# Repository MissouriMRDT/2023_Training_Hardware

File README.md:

# 2023_Training_Hardware
Useless Schematics and PCB Layouts for Training Purposes

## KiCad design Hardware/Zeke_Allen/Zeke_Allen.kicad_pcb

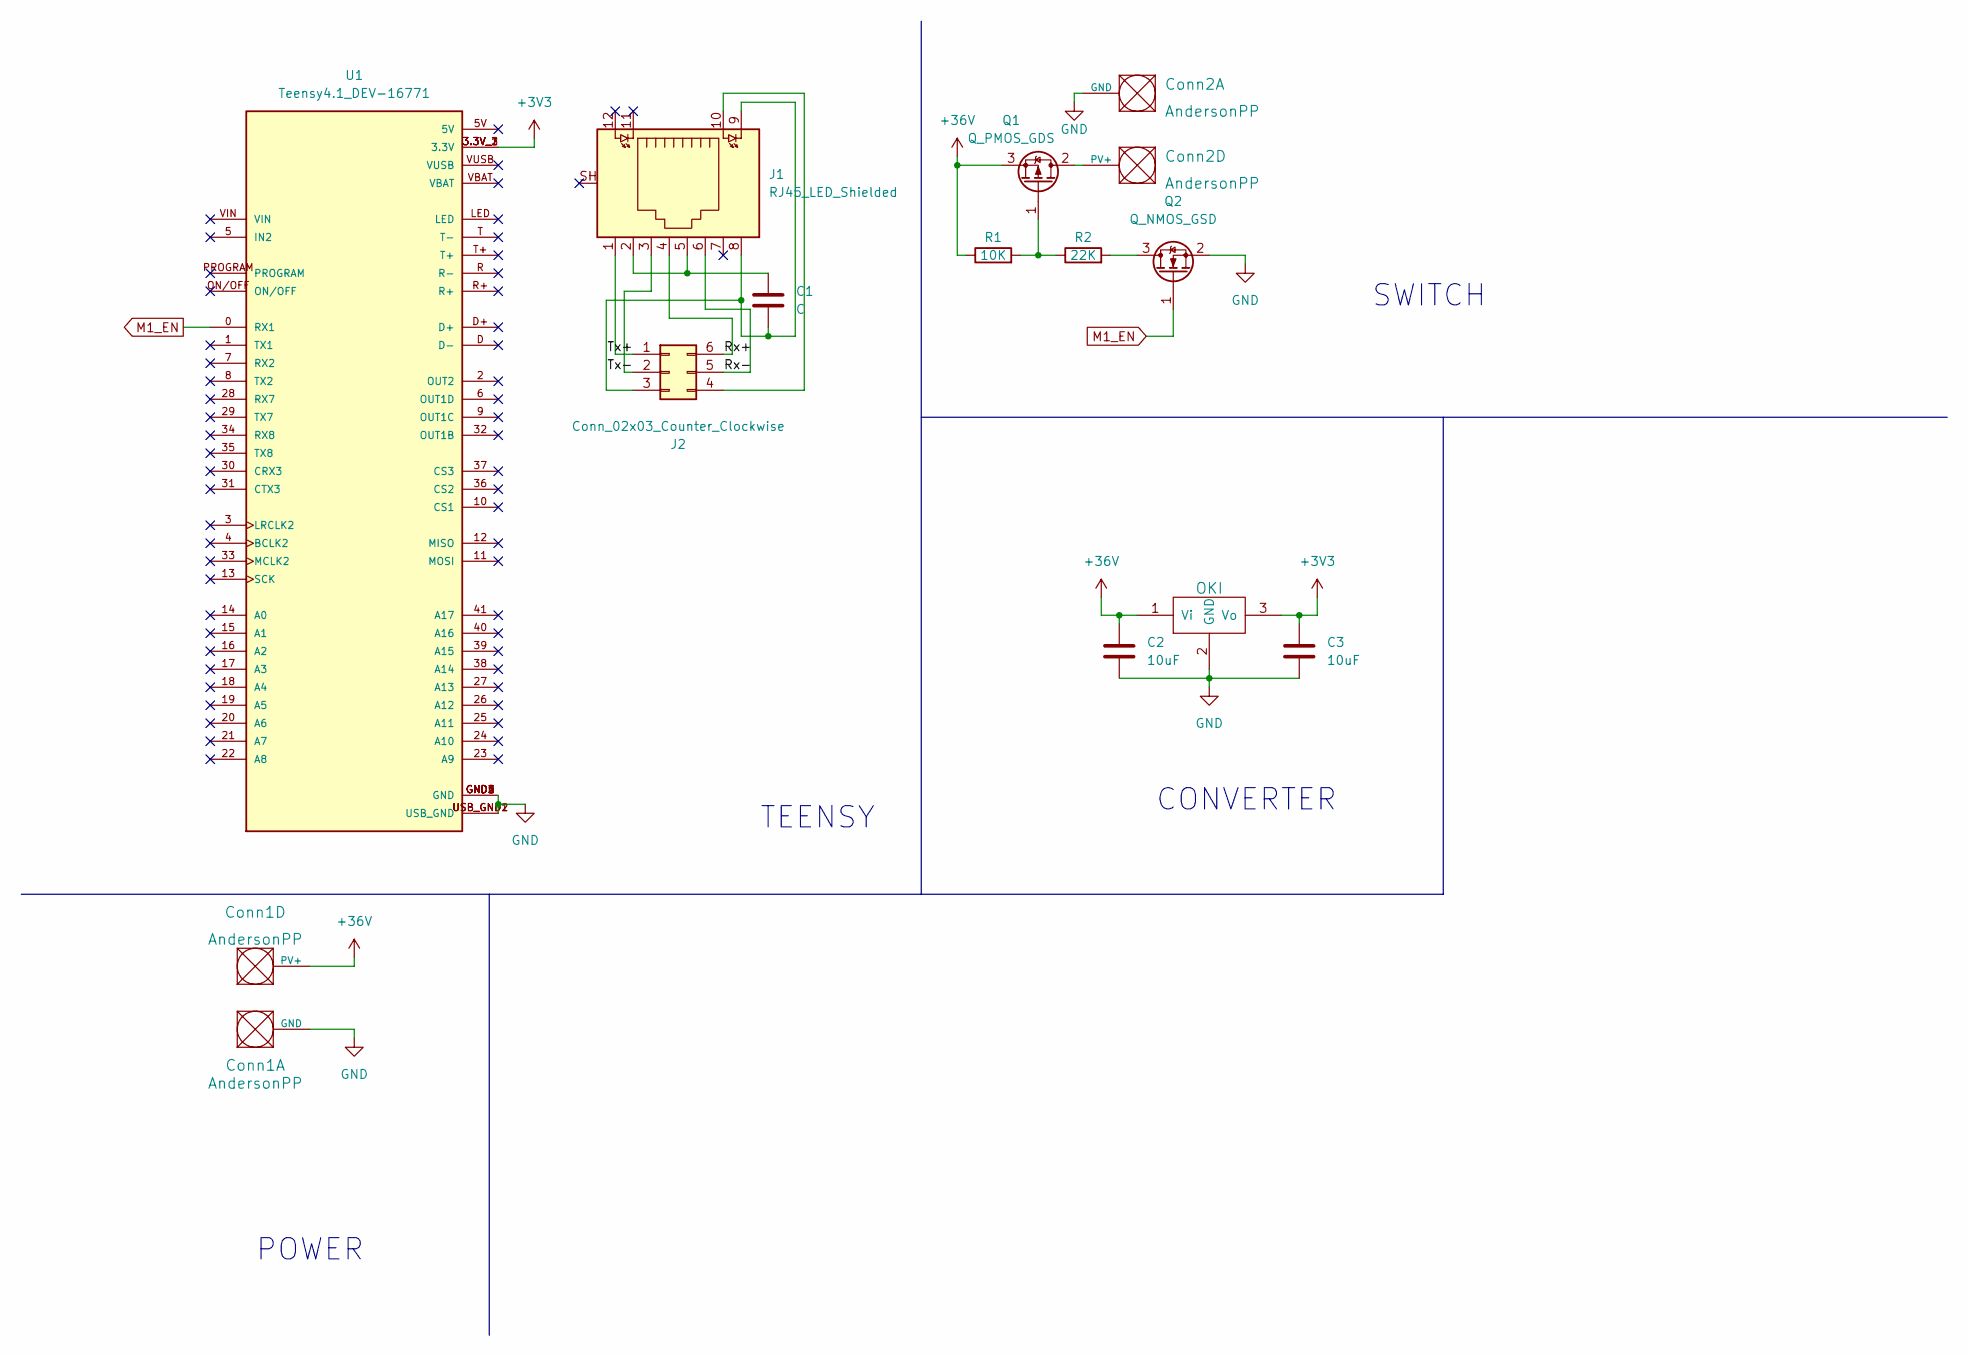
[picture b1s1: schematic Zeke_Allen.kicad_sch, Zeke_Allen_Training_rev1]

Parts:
C1: C; C_0603_1608Metric_Pad1.08x0.95mm_HandSolder
C2, C3: 10uF; C_0603_1608Metric_Pad1.08x0.95mm_HandSolder
Conn1, Conn2: AndersonPP; Square_Anderson_2_H_Side_By_Side_PV
J1: RJ45_LED_Shielded; RJ45_Teensy
J2: Conn_02x03_Counter_Clockwise; PinHeader_2x03_P2.00mm_Vertical
Q1: Q_PMOS_GDS; TO-252-2
Q2: Q_NMOS_GSD; SOT-23
R1: 10K; R_0603_1608Metric_Pad0.98x0.95mm_HandSolder
R2: 22K; R_0603_1608Metric_Pad0.98x0.95mm_HandSolder
U1: Teensy4.1_DEV-16771; Teensy_4_1_Vertical; PARTREV 4.1
U2: OKI; OKI_Horizontal

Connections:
+3V3: C3.1, U1.3.3V_1 (3.3V), U1.3.3V_2 (3.3V), U1.3.3V_3 (3.3V), U2.3 (Vo)
+36V: C2.1, Conn1.4 (PV+), Q1.3 (S), R1.1, U2.1 (Vi)
/Rx+: J1.4, J2.6
/Rx-: J1.6, J2.5
/Tx+: J1.1, J2.1
/Tx-: J1.3, J2.2
GND: C2.2, C3.2, Conn1.1 (GND), Conn2.1 (GND), Q2.2 (S), U1.GND1 (GND), U1.GND2 (GND), U1.GND3 (GND), U1.GND4 (GND), U1.GND5 (GND), U1.USB_GND1 (USB_GND), U1.USB_GND2 (USB_GND), U2.2 (GND)
M1_EN: Q2.1 (G), U1.0 (RX1)
unnamed: C1.1, J1.2, J1.5
unnamed: C1.2, J1.8, J1.9, J2.3
unnamed: Conn2.4 (PV+), Q1.2 (D)
unnamed: J1.10, J2.4
unnamed: Q1.1 (G), R1.2, R2.1
unnamed: Q2.3 (D), R2.2

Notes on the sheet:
SWITCH
TEENSY
POWER
CONVERTER

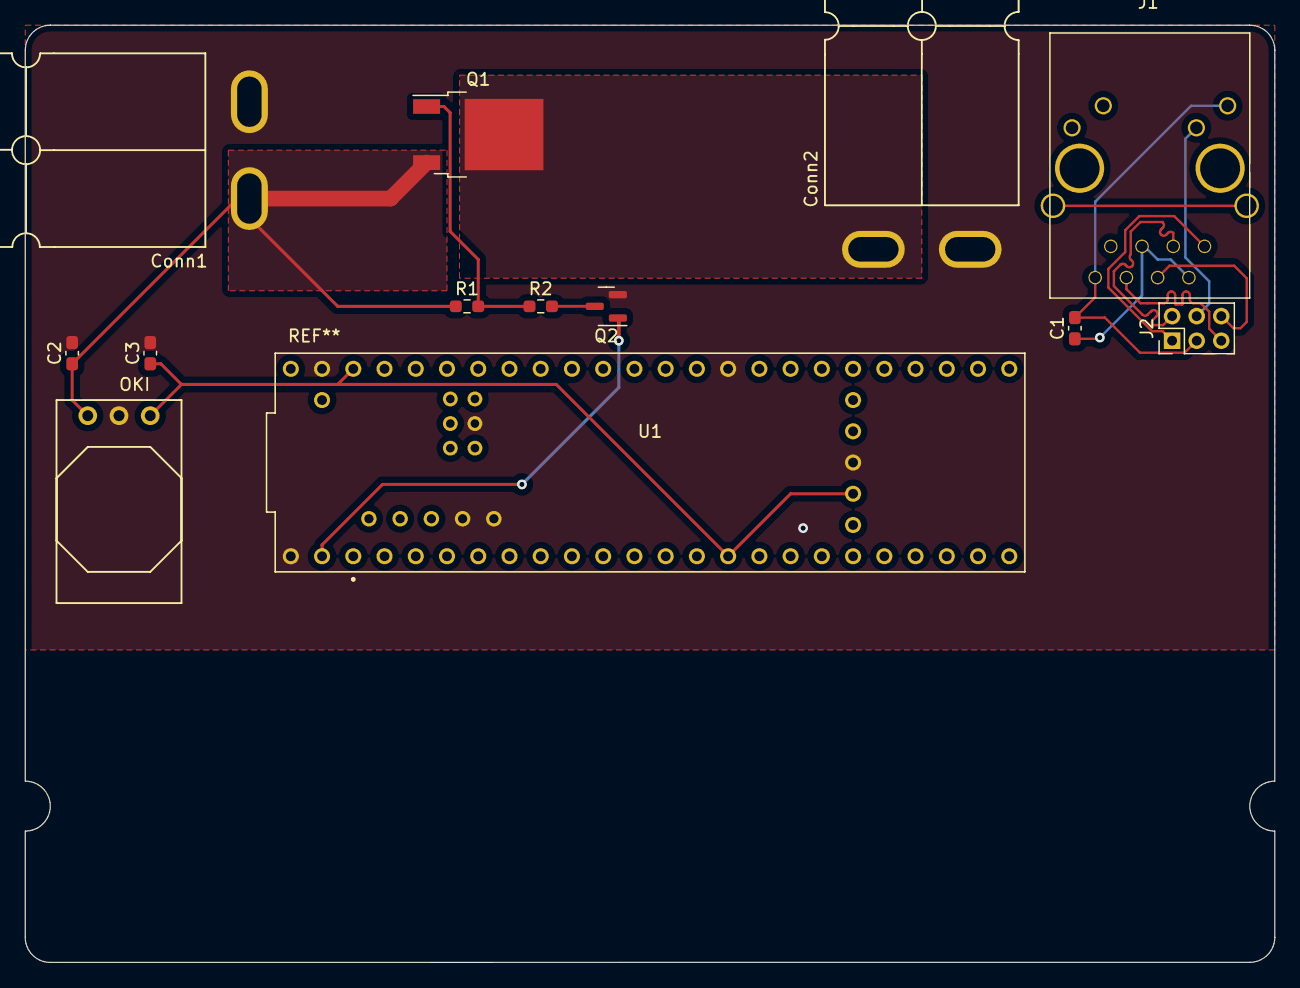
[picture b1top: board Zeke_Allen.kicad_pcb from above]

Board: 2 copper layers, 101.6 x 76.2 mm, 13 parts (0 on the bottom side), 14 nets.

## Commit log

2022-09-04 finished training hardware
2022-09-04 Finished training hardware schematic
2022-09-04 Training complete
2022-09-04 Useless Motor
    why
2022-09-04 Completed Training Hardware
2022-10-02 finished layout training
2022-10-02 Layout Training
2022-10-02 layout shtuff
2022-10-02 Made Layout
    Added Footprints. Made Layout.
2022-10-02 layout
2022-10-02 PCB Layout Training
